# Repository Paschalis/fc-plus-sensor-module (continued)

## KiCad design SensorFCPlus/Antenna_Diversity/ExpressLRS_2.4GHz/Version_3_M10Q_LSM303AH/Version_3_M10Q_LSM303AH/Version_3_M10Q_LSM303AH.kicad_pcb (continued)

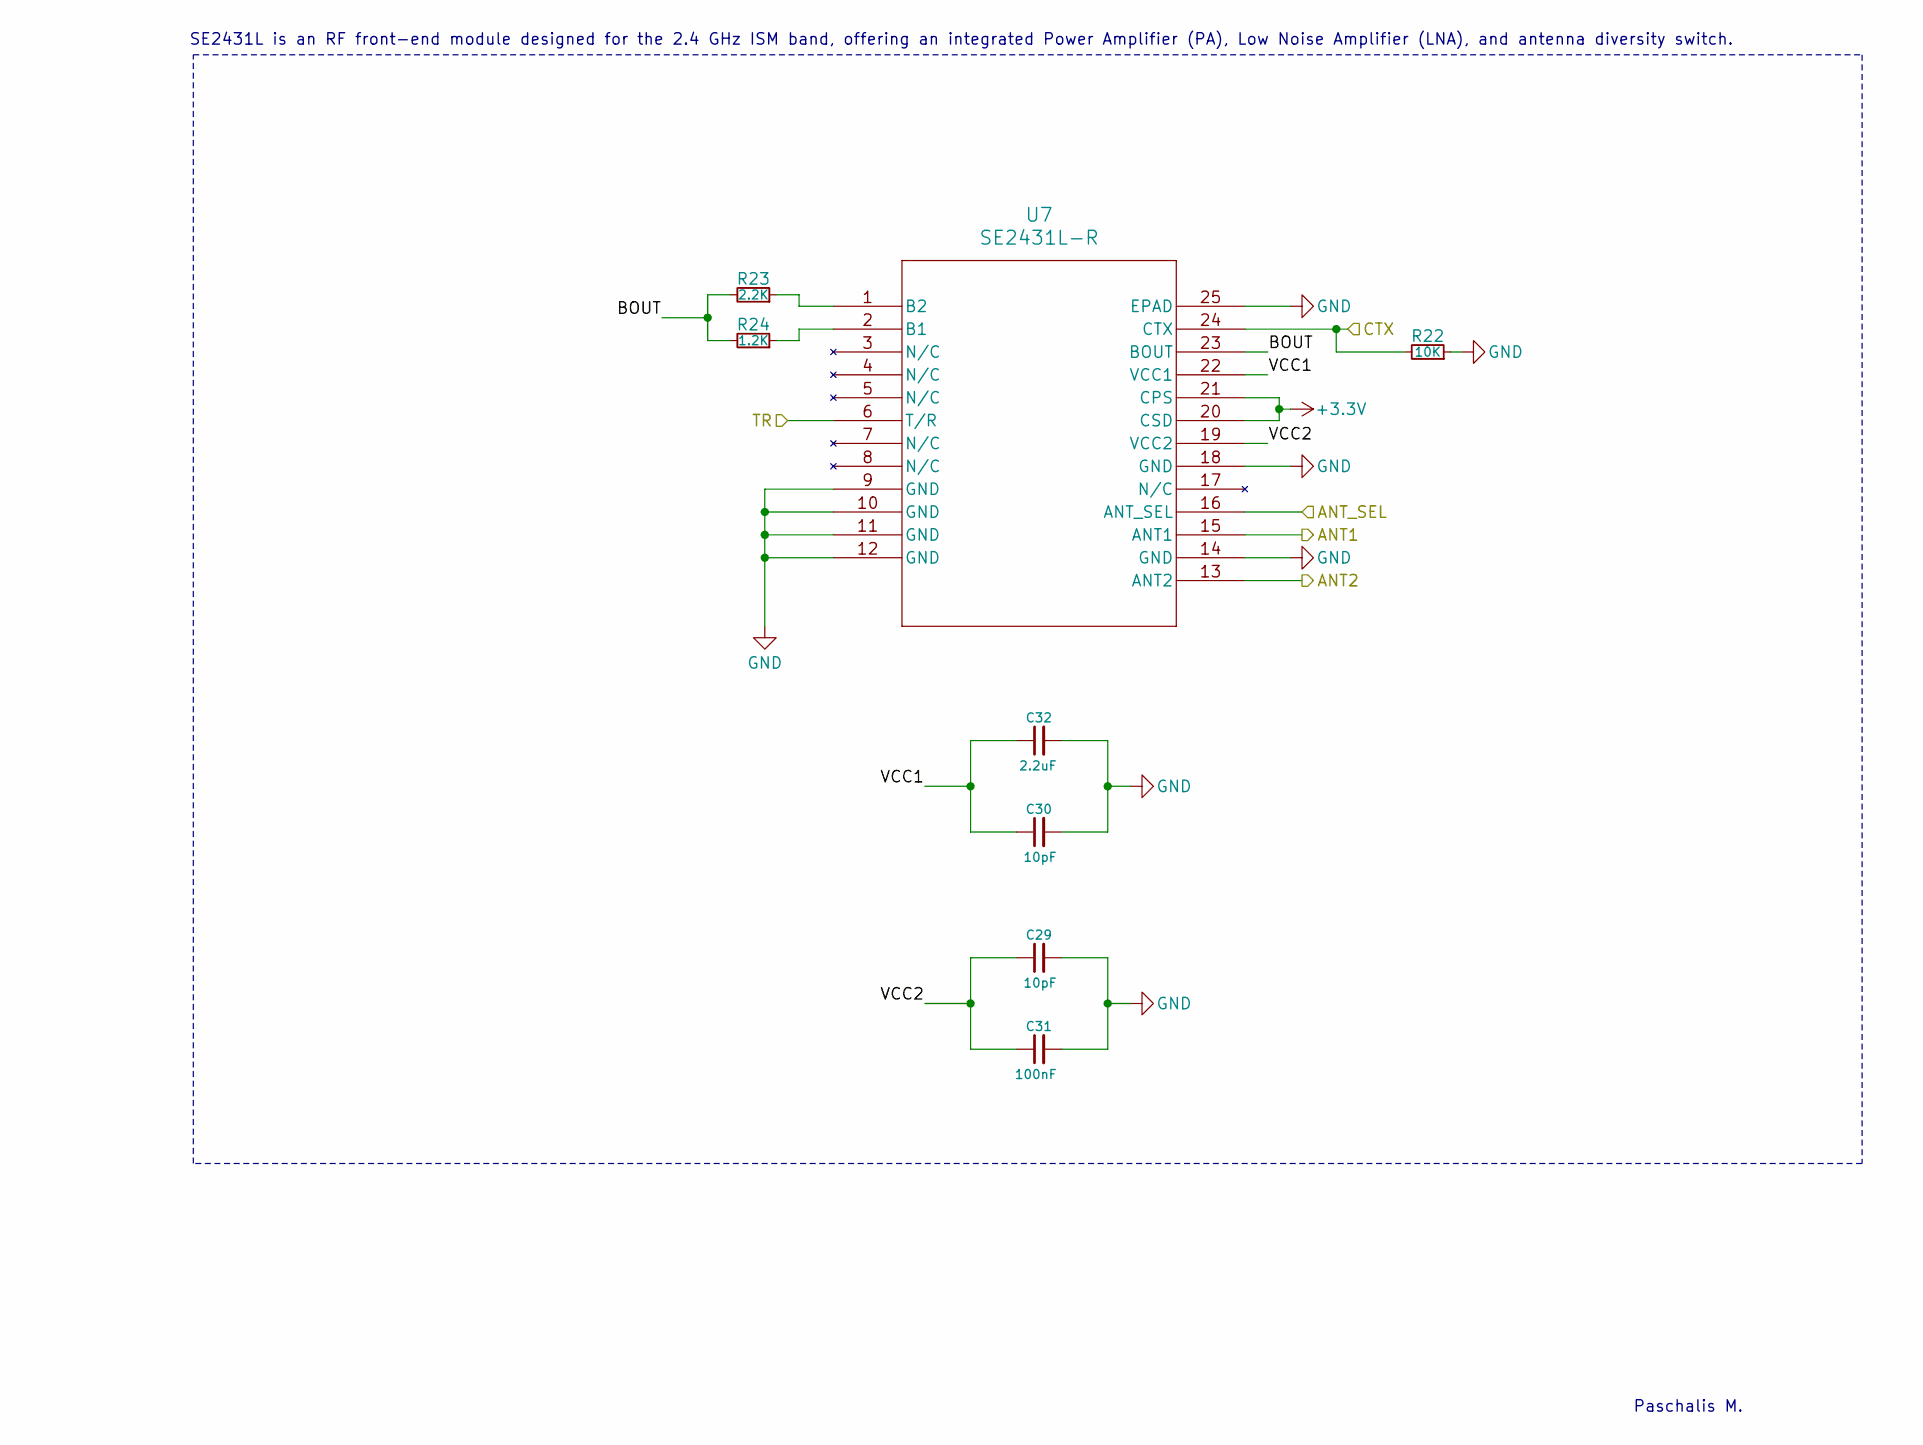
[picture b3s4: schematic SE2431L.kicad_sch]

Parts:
C29, C30: 10pF; C_0603_1608Metric_Pad1.08x0.95mm_HandSolder
C31: 100nF; C_0603_1608Metric_Pad1.08x0.95mm_HandSolder
C32: 2.2uF; C_0603_1608Metric_Pad1.08x0.95mm_HandSolder
R22: 10K; R_0603_1608Metric_Pad0.98x0.95mm_HandSolder
R23: 2.2K; R_0603_1608Metric_Pad0.98x0.95mm_HandSolder
R24: 1.2K; R_0603_1608Metric_Pad0.98x0.95mm_HandSolder
U7: SE2431L-R; SE2431L_SKY

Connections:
+3.3V: U7.20 (CSD), U7.21 (CPS); also elsewhere on the board
/ESP8285/ANT_SEL: U7.16 (ANT_SEL); also elsewhere on the board
/ESP8285/CTX: R22.2, U7.24 (CTX); also elsewhere on the board
/SE2431L/ANT1: U7.15 (ANT1); also elsewhere on the board
/SE2431L/ANT2: U7.13 (ANT2); also elsewhere on the board
/SE2431L/BOUT: R23.2, R24.2, U7.23 (BOUT)
/SE2431L/TR: U7.6 (T/R); also elsewhere on the board
/SE2431L/VCC1: C30.1, C32.1, U7.22 (VCC1)
/SE2431L/VCC2: C29.1, C31.1, U7.19 (VCC2)
GND: C29.2, C30.2, C31.2, C32.2, R22.1, U7.9 (GND), U7.10 (GND), U7.11 (GND), U7.12 (GND), U7.14 (GND), U7.18 (GND), U7.25 (EPAD); also elsewhere on the board
unnamed: R24.1, U7.2 (B1)
unnamed: R23.1, U7.1 (B2)

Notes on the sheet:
Paschalis M.
SE2431L is an RF front-end module designed for the 2.4 GHz ISM band, offering an integrated Power Amplifier (PA), Low Noise Amplifier (LNA), and antenna diversity switch.

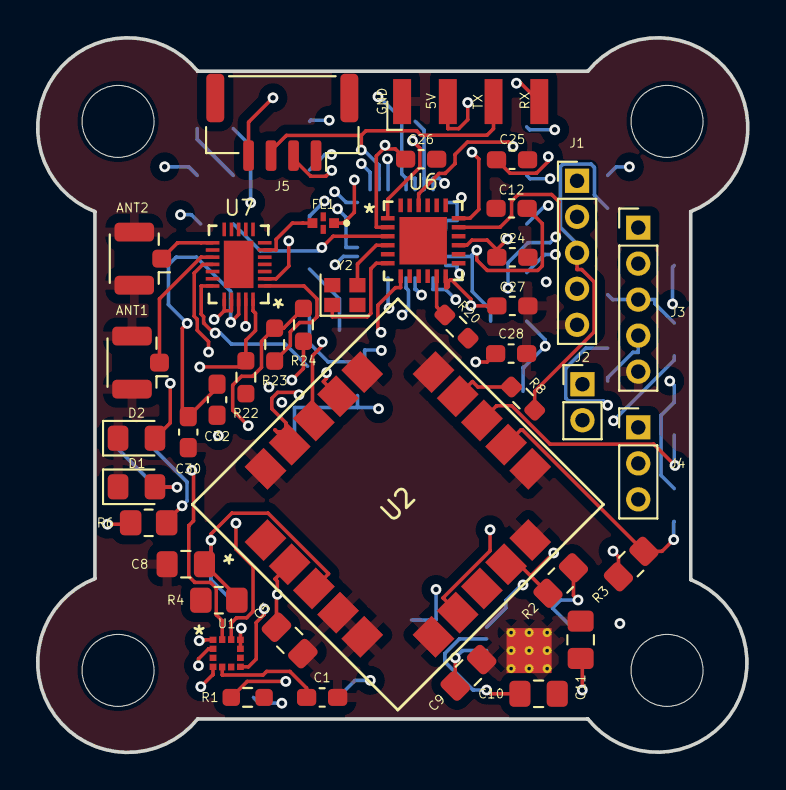
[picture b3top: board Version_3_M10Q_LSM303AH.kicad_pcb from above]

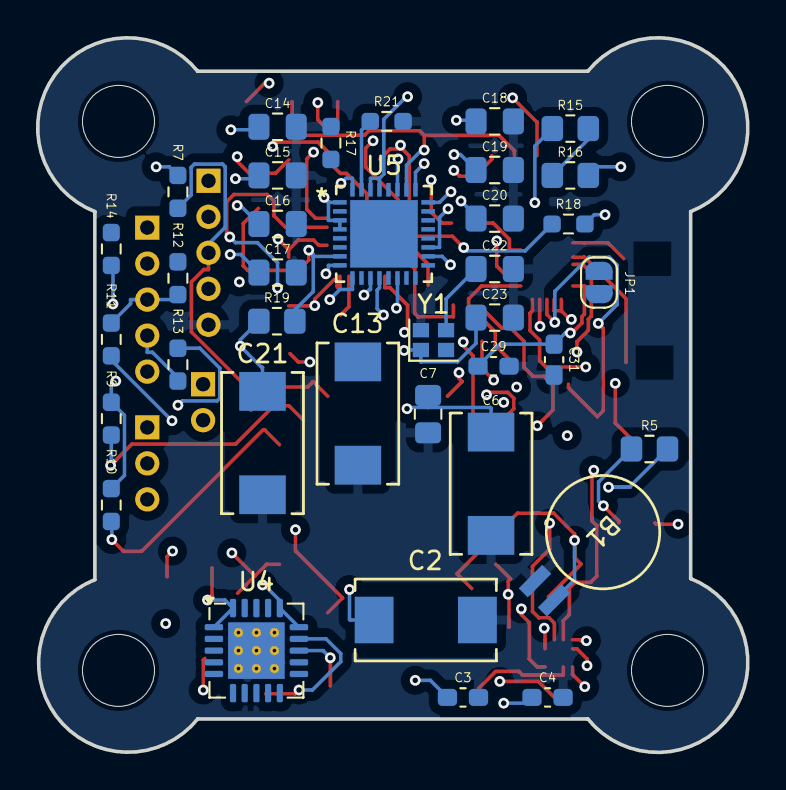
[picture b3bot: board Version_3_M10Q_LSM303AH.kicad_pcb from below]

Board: 4 copper layers, 39.4 x 39.7 mm, 81 parts (37 on the bottom side), 59 nets.

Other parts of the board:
hole1, hole2, hole3, hole4: MountingHole_4mm

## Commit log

2024-12-22 Add .gitignore for KiCad PCB project to exclude temporary and exported files
2024-12-26 Added datasheets for components and sensors
2024-12-26 Added HMC5883L and QMC5883L to schematic
2025-01-01 Add SensorFCPlus setup with ExpressLRS 2.4GHz and version 3 M10Q LSM303AH configuration
2025-01-01 Updated README with Related Projects and License Information
2025-01-01 Added preview image
2025-01-04 Add ExpressLRS 900MHz Version 3 with M10Q and LSM303AH support
2025-01-05 Added SX1276-77-78-79 and TPS7A20 datasheets~
2025-01-06 Added datasheets for SE2435L and TPS7A47 to the ExpressLRS 900MHz documentation
2025-01-08 Update README with Transmission Modes Classification.
2025-01-08 Remove outdated KiCad project files for ExpressLRS 2.4GHz across all versions.
2025-01-08 Remove outdated KiCad project files for ExpressLRS 900MHz across all versions.
2025-01-08 Revert "Update README with Transmission Modes Classification."
    This reverts commit 2d5c678ea4eb258418c94a3ba9c42b639ba6ef91.
2025-01-08 Update preview image
2025-01-10 Remove outdated KiCAD project files
2025-01-13 Added "Go Back to Main README" button at the bottom of "Transmission Modes Classification" README
2025-01-14 Updated and cleaned up datasheets for 900MHz and 2.4GHz components
2025-01-15 Update KiCad files for ExpressLRS modules
    - Modified:
    - 2.4GHz Version 3 (M10Q LSM303AH) project and schematic files
    - 900MHz Version 3 (M10Q LSM303AH) schematic files for ESP8285 and SE2435L
    - Added:
    - 2.4GHz Version 3 schematics: ESP8285, SE2431, SE2431L, SX1280
2025-01-20 Update KiCad schematic and project files for ExpressLRS 2.4GHz modules (Version 1 and 2) and add new components (ESP8285, SE2431L, SX1280)
2025-01-23 Update README for Version 3 M10Q LSM303AH board
2025-01-23 Add MAX-M10S DataSheet and SAM-M10Q DataSheet to documentation
2025-01-23 Add image folder for Antenna Diversity Version 3 M10Q LSM303AH
2025-01-23 Track large files using Git LFS
2025-01-23 Add Board Designs Overview section and related Custom RX/TX Board Designs for GCS Communication project
2025-01-23 Update PCB design for Version 3 M10Q LSM303AH (ESP8285, SE2431L, SX1280, and main board)
2025-01-23 Updated README with board categories and PCB color information for better identification
2025-01-25 Replaced GIF with a smaller version to reduce size
2025-01-25 Created a site to place the modules
2025-01-25 Updated module order in index.html and added site link to README.md
2025-01-25 Centered the site link badge in README.md
2025-01-26 Adjust module size and add spacing
    - Reduced module max-width to 400px.
    - Added space above footer and below container.
2025-01-28 Removed a small arrow from 'Receiver' in diversity.png
2025-01-28 Updated documentation link in index.html
2025-02-02 Update README.md and Version 2 files; add new GIF and MP4 for Version 2
2025-02-17 Updated README and V1 M10Q HMC5883L KiCad files, added documentation and media
2025-02-18 Updated Version_3_M10Q_LSM303AH
2025-02-18 Added PCB preview image and updated README
2025-02-21 Added RFX2401C datasheet for ExpressLRS 2.4GHz module
2025-02-23 Added datasheets for ExpressLRS communication module, ESP32-PICO-D4, and w3008 antenna
2025-03-05 Updated Version 1 files: schematics, project, README, and preview image
2025-03-05 Added Version 2 files: README and preview image
2025-03-11 Added preview images above module videos
2025-03-16 Add True Diversity module and update README
2025-03-16 Update preview.png: Replace 'Under Construction' label with final schematic
